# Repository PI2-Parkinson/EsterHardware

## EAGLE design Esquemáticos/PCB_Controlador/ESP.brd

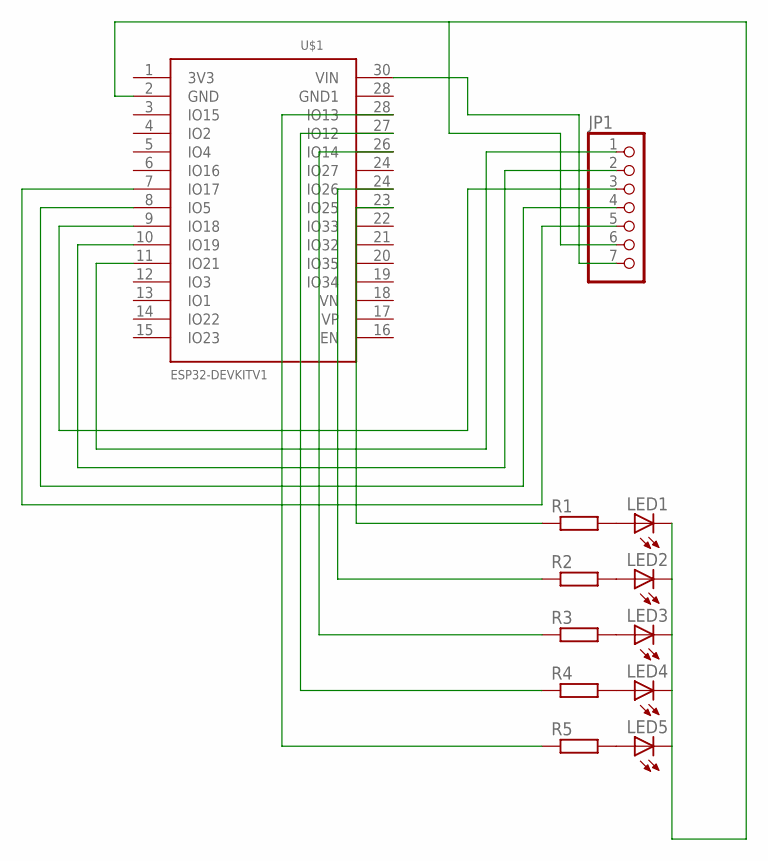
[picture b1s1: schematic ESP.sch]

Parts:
JP1: PINHD-1X7; 1X07
LED1, LED2, LED3, LED4, LED5: LED5MM
R1, R2, R3, R4, R5: R-EU_0207/7; 0207/7
U$1: ESP32DEVKITV1; ESP32-DEVKITV1

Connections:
unnamed: JP1.7, U$1.30 (VIN)
unnamed: JP1.6, LED1.K (C), LED2.K (C), LED3.K (C), LED4.K (C), LED5.K (C), U$1.2 (GND)
unnamed: R2.1, U$1.24 (IO27)
unnamed: JP1.1, U$1.11 (IO21)
unnamed: JP1.2, U$1.10 (IO19)
unnamed: JP1.3, U$1.9 (IO18)
unnamed: JP1.4, U$1.8 (IO5)
unnamed: LED1.A, R1.2
unnamed: LED2.A, R2.2
unnamed: LED3.A, R3.2
unnamed: LED4.A, R4.2
unnamed: LED5.A, R5.2
unnamed: JP1.5, U$1.7 (IO17)
unnamed: R1.1, U$1.23 (IO25)
unnamed: R3.1, U$1.26 (IO14)
unnamed: R4.1, U$1.27 (IO12)
unnamed: R5.1, U$1.28 (IO13)

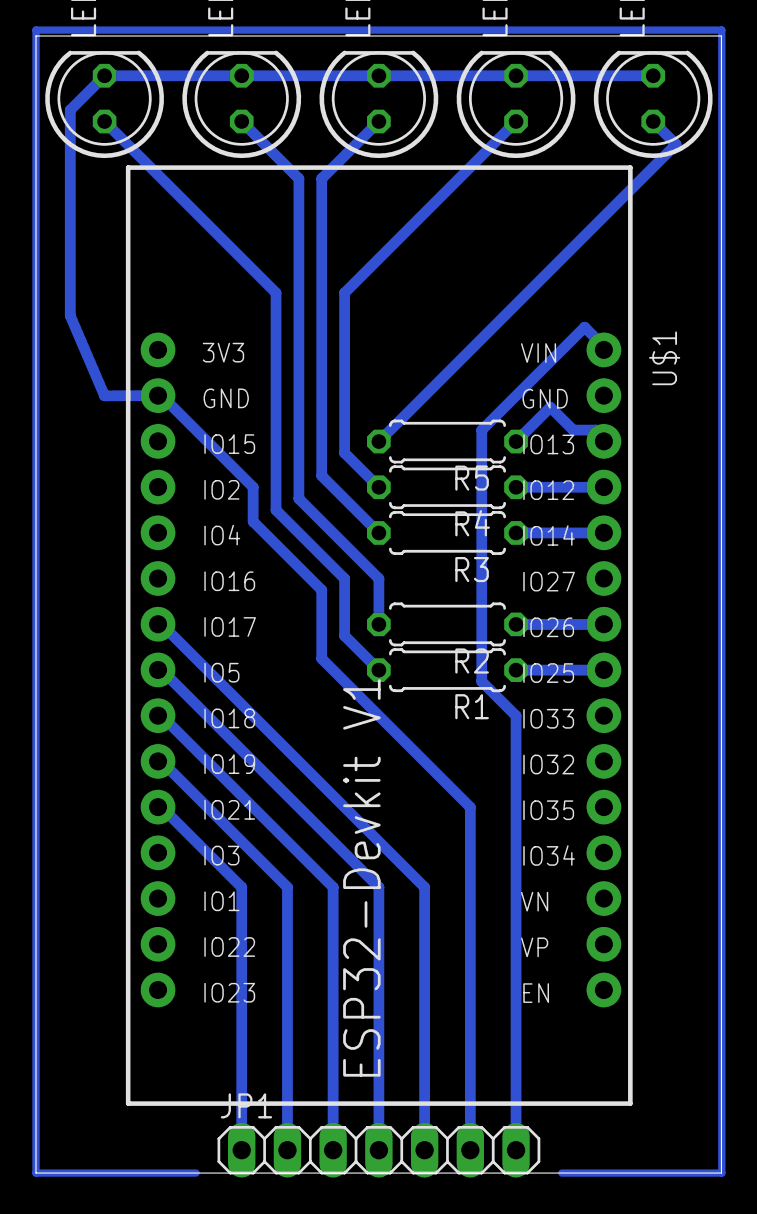
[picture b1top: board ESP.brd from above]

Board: 2 copper layers, 38.1 x 63.2 mm, 12 parts (0 on the bottom side), 17 nets.

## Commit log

2019-10-18 Rename Esfera_principal.c to Códigos em C/Esfera_principal.c
2019-10-18 Rename Esfera_secundaria.c to Código em C/Esfera_secundaria.c
2019-10-18 Rename Código em C/Esfera_secundaria.c to Códigos em C/Esfera_secundaria.c
2019-10-18 Rename uMQTT_Broker.ino to Com_Principal_Secundario/uMQTT_Broker.ino
2019-10-18 Rename Controle_base.c to Códigos em C/Controle_base.c
2019-10-18 Rename ester_wifi_principal.ino to ester_principal.ino
2019-10-29 Create COM_mqtt_princ_base_v2
2019-10-30 Rename Controlador_Principal_BLE_e_fWifi.ino to Codigos_pronto_swifi/Controlador_Principal_BLE_e_fWifi.ino
2019-10-30 Rename Codigos_pronto_swifi/Controlador_Principal_BLE_e_fWifi.ino to Codigos_pronto_sem_wifi/Controlador_Principal_BLE_e_fWifi.ino
2019-11-01 Rename Controlador_Principal_BLE_e_Wifi.ino to Códigos Completos/Controlador_Principal_BLE_e_Wifi.ino
2019-12-04 Upload files
2019-12-04 Colocou os códigos nas pastas e tirou o SR do jogo 1
2019-12-04 Adicionado restante dos arquivos de eletrônica.
2019-12-04 Imagens de testes do subsistema
